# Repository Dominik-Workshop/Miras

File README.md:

# Miras

## Overview

Autonomous minisumo robot, based around an **STM32** microcontroller and **VL53L0X** TOF (time of flight) distance sensors, which provide necessary processing power and great detection range of opponents.

Its distinguishing feature is a set of **deployable wings**, designed to attract an opponent toward them, making them vulnerable to falling off the dohyo.

## Electronics

This project features two custom-designed PCBs that are connected via a flexible flat cable (FFC):

- [**Main board**](/pcb_main/): responsible for the robot's core functionalities. It integrates the microcontroller, sensors, motor drivers, and power management circuitry

- [**Top board**](/pcb_top/): accommodates an on/off switch, an SWD programming connector, configuration DIP switches, and a dedicated space for a standard [starter module](https://p1r.se/startmodule/)

The robot also features a 128x64px **OLED** screen for debugging.

## Mechanical

The chassis is a robust blend of 3D-printed components, steel, and aluminum, designed for durability and a low center of gravity. For superior traction on the dohyo, the robot is equipped with custom cast rubber tires. The unique deployable wings, made from lightweight paper, serve as the active deflection mechanism.

The robot is powered by two **N20** motors.

## Used Tools

- [Autodesk EAGLE](https://www.autodesk.com/products/eagle/) - Schematic and PCB design
- [Autodesk Inventor](https://www.autodesk.com/products/inventor/) - 3D modeling
- [STM32CubeIDE](https://www.st.com/en/development-tools/stm32cubeide.html) - STM32 firmware development (build/flash/debug)

## Authors

- [**Dominik Pluta**](https://github.com/Dominik-Workshop):
  - **Responsibility**: PCB design, programming
- [**Kamil Winnicki**](https://github.com/KamilWuu):
  - **Responsibility**: design and manufacturing of mechanical parts

## Special Thanks

Special thanks to [**Eryk Możdzeń**](https://github.com/Eryk-Mozdzen), who helped with programming.

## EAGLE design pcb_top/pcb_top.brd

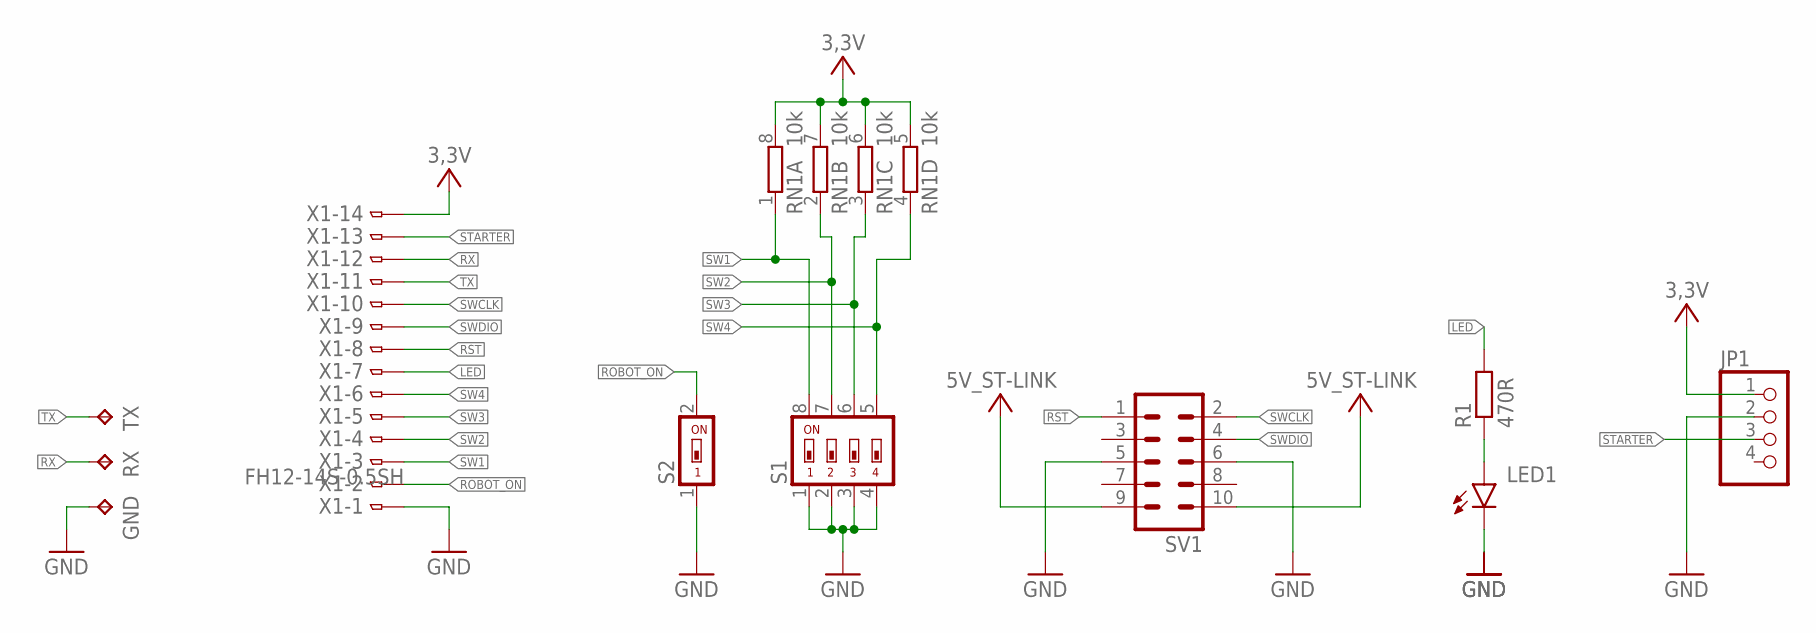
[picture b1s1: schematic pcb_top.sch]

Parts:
GND: TPTP20SQ; TP20SQ
JP1: PINHD-1X4; 1X04
LED1: LEDCHIP-LED0805; CHIP-LED0805
R1: 470R; R0603
RN1: 10k; CAT16
RX: TPTP20SQ; TP20SQ
S1: SWS004; SMS-004
S2: SWS001; SMS-001
SV1: ML10
TX: TPTP20SQ; TP20SQ
X1: FH12-14S-0.5SH

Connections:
3,3V: JP1.1, RN1.5 (2), RN1.6 (2), RN1.7 (2), RN1.8 (2), X1.14
5V_ST-LINK: SV1.9, SV1.10
GND: GND.TP, JP1.2, LED1.C, S1.1, S1.2, S1.3, S1.4, S2.1, SV1.5, SV1.6, X1.1
LED: R1.2, X1.7
unnamed: LED1.A, R1.1
ROBOT_ON: S2.2, X1.2
RST: SV1.1, X1.8
RX: RX.TP, X1.12
STARTER: JP1.3, X1.13
SW1: RN1.1, S1.8, X1.3
SW2: RN1.2 (1), S1.7, X1.4
SW3: RN1.3 (1), S1.6, X1.5
SW4: RN1.4 (1), S1.5, X1.6
SWCLK: SV1.2, X1.10
SWDIO: SV1.4, X1.9
TX: TX.TP, X1.11

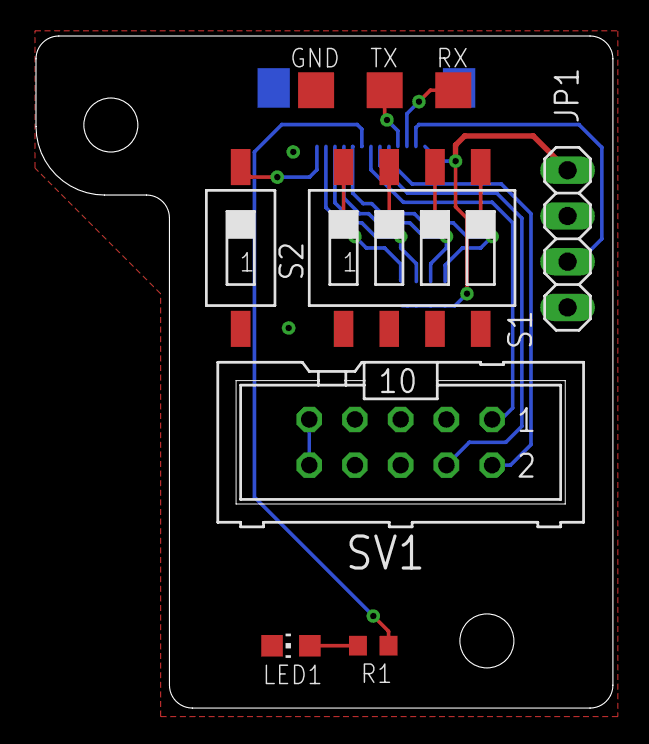
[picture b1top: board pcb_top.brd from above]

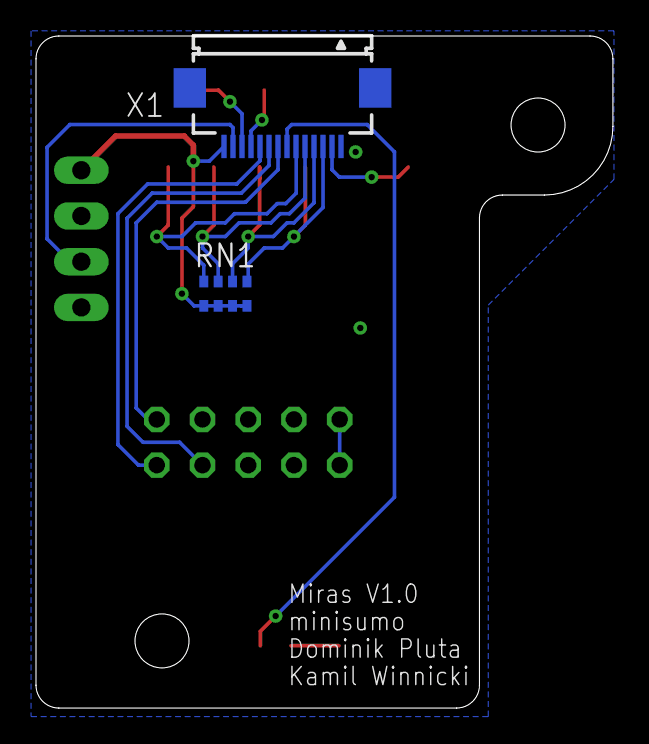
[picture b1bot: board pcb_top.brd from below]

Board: 2 copper layers, 32.0 x 37.3 mm, 11 parts (2 on the bottom side), 16 nets.

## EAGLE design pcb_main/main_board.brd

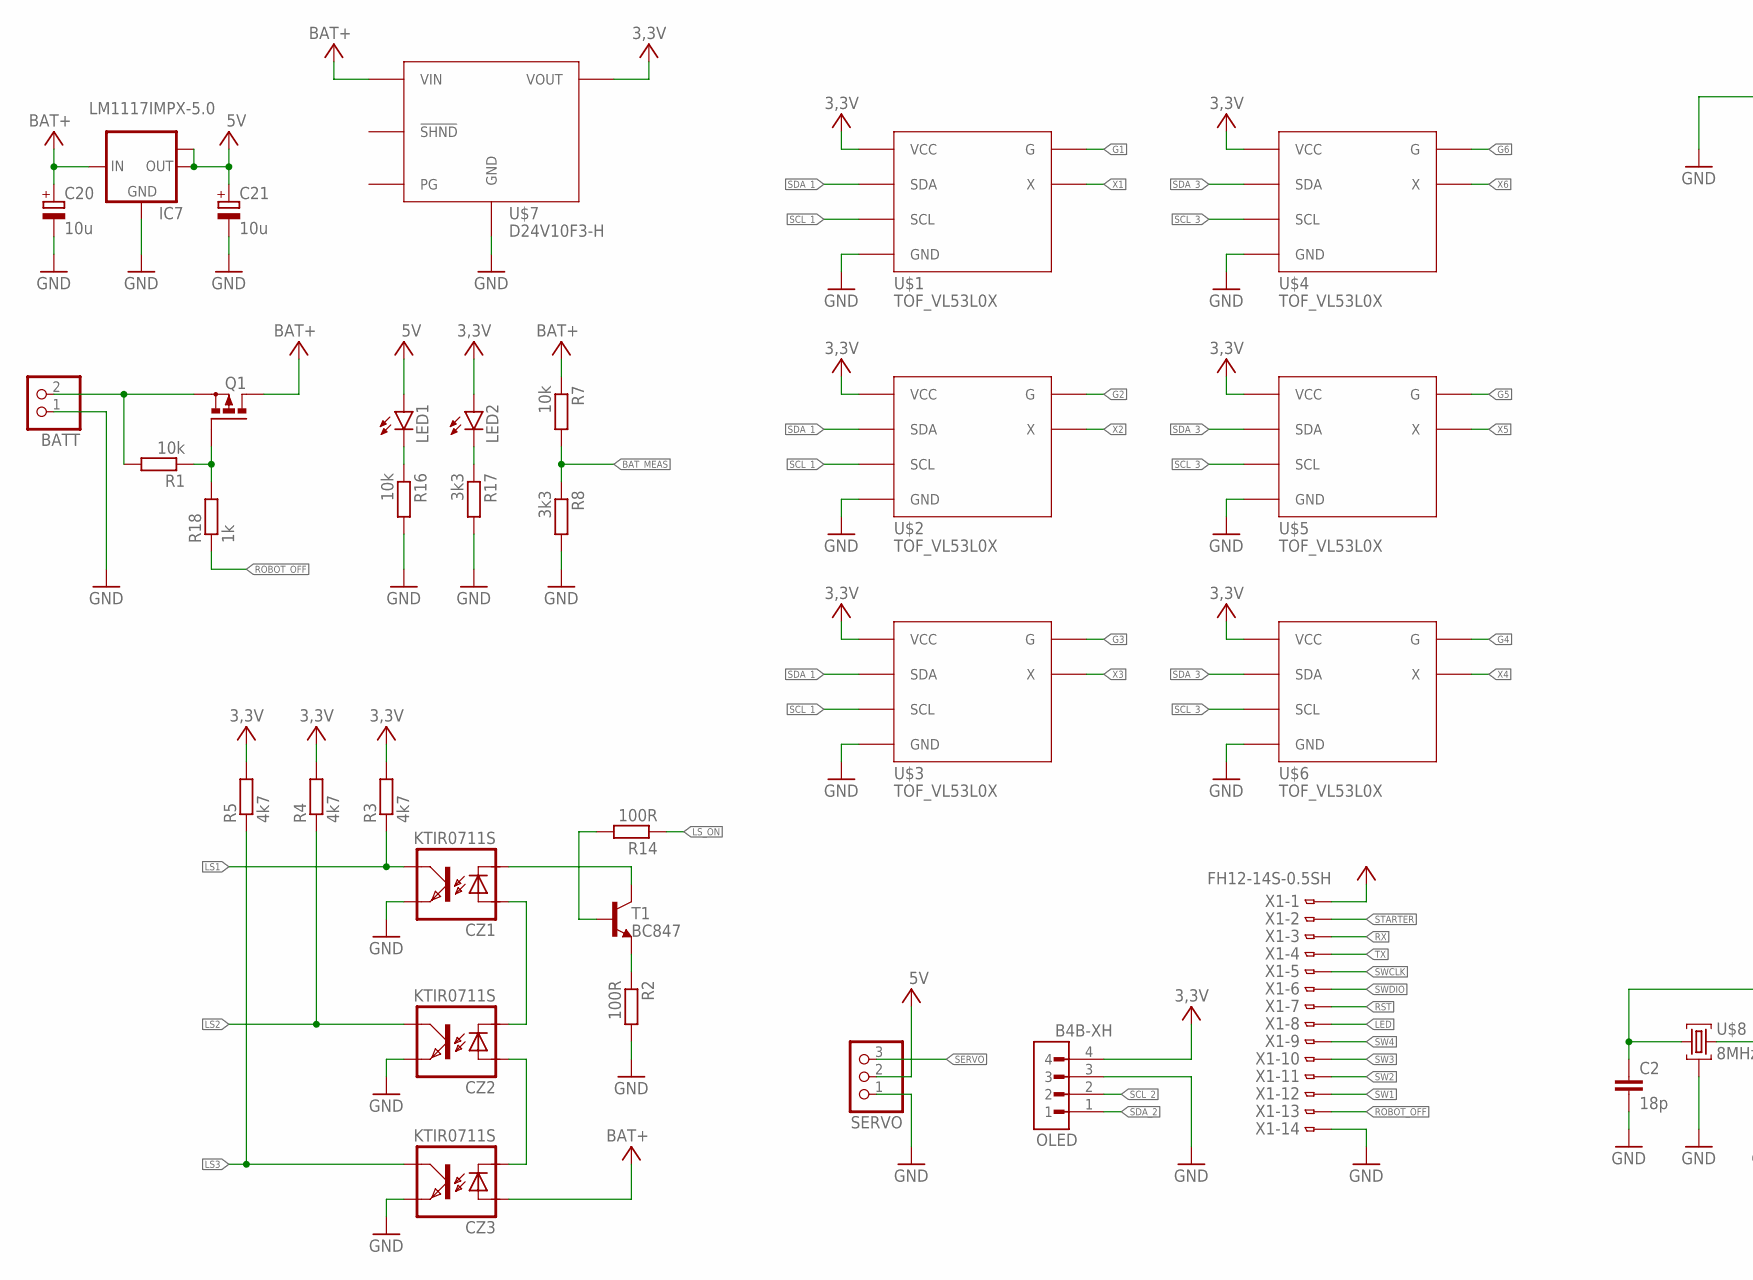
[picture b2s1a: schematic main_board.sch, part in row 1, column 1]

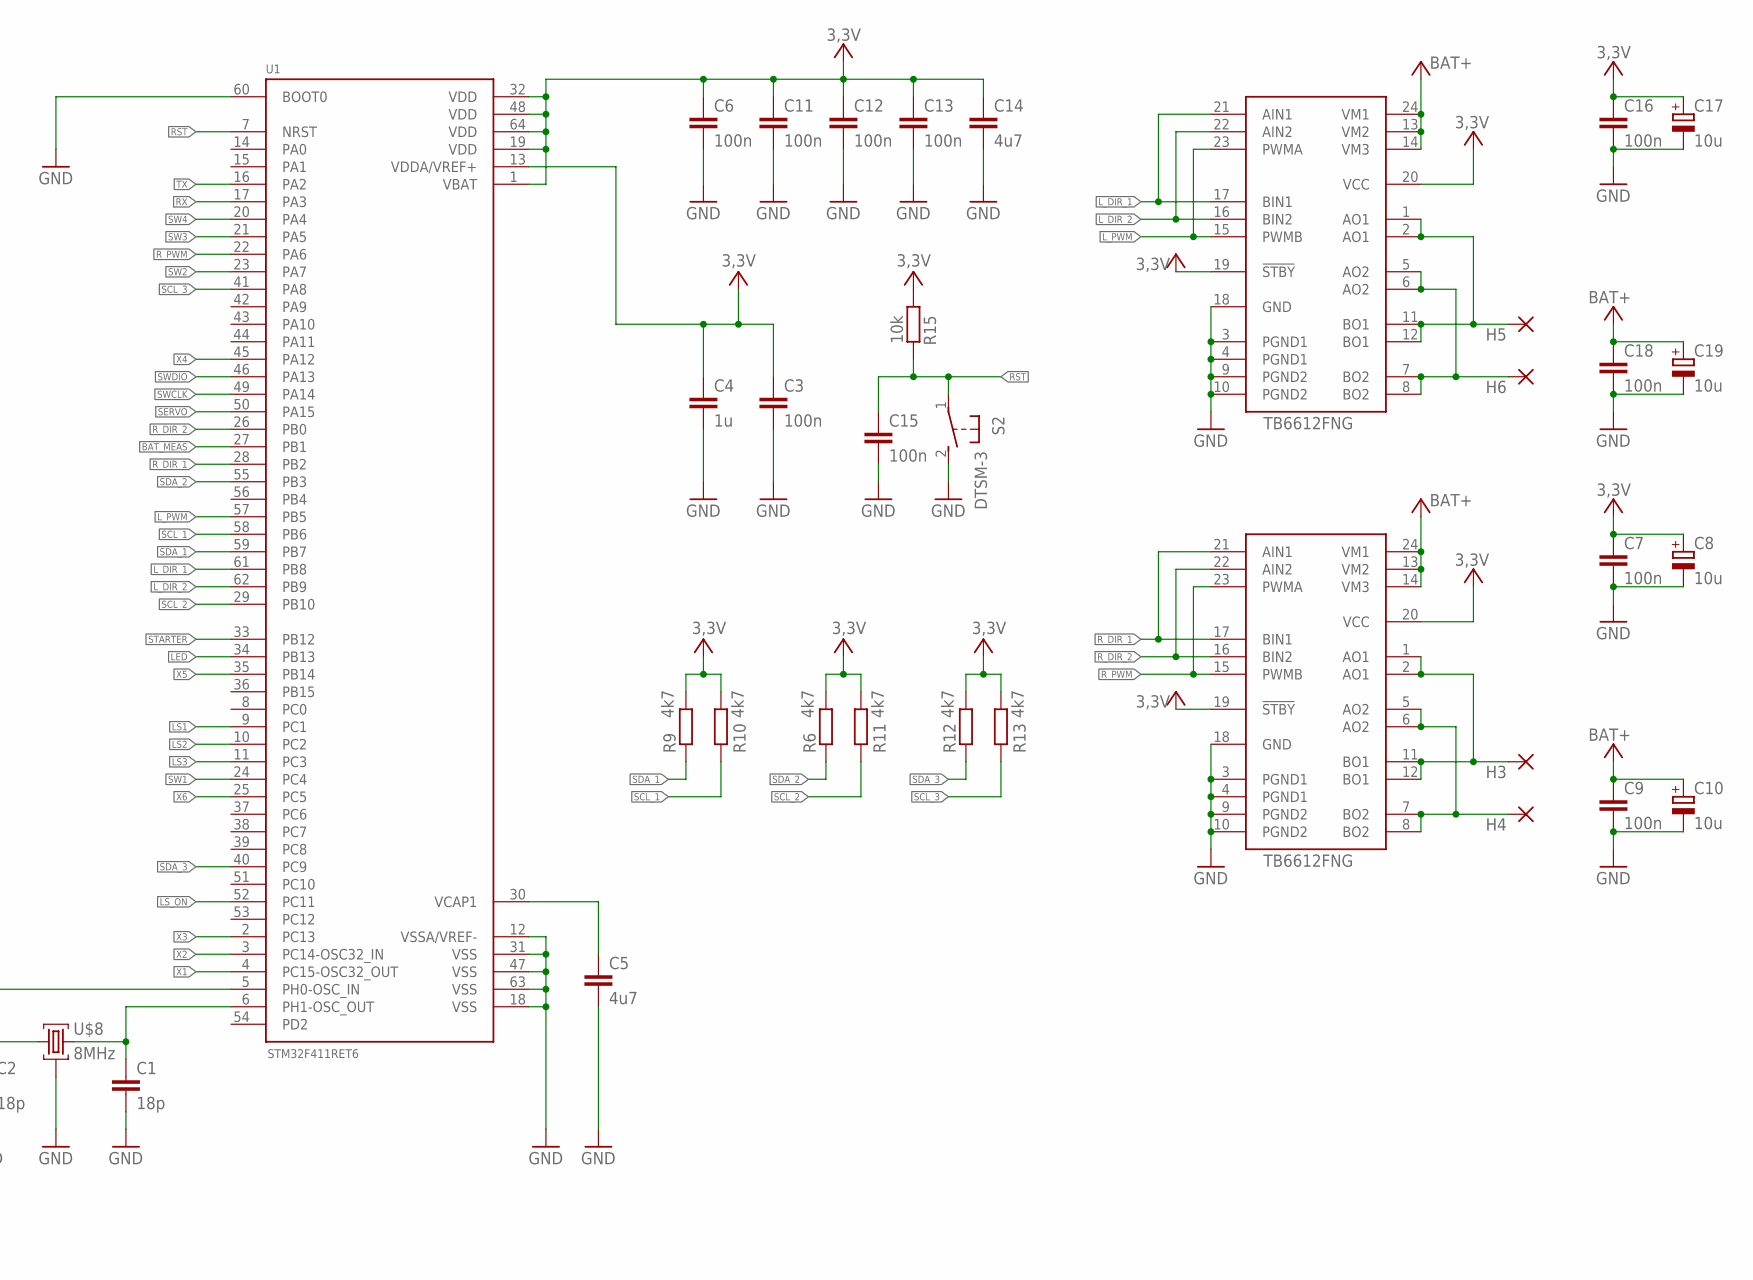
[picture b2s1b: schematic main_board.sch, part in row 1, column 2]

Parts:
BATT: PINHD-1X2; 1X02
C1, C2: 18p; C0603
C3, C6, C7, C9, C11, C12, C13, C15, C16, C18: 100n; C0603
C4: 1u; C0603
C5, C14: 4u7; C0603
C8, C10, C17, C19, C20, C21: 10u; B/3528-21W
CZ1, CZ2, CZ3: KTIR0711S; TOP
H3, H4, H5, H6: 1,6/0,8
IC7: LM1117IMPX-5.0; SOT223
LED1, LED2: LEDCHIPLED_0603; CHIPLED_0603
OLED: B4B-XH; JST_B4B-XH-A(LF)(SN)
Q1: P-MOSFET-SO8; SO-08
R1, R7, R15, R16: 10k; R0603
R2, R14: 100R; R0603
R3, R4, R5, R6, R9, R10, R11, R12, R13: 4k7; R0603
R8, R17: 3k3; R0603
R18: 1k; R0603
S2: DTSM-3
SERVO: PINHD-1X3; 1X03
T1: BC847; SOT23
TB6612, TB6612_: TB6612FNG; SSOP24
U1: STM32F411RET6; QFP50P1200X1200X160-64N
U$1, U$2, U$3, U$4, U$5, U$6: TOF_VL53L0X
U$7: D24V10F3-H
U$8: 8MHz; CRYSTAL_3,4X2,7
X1: FH12-14S-0.5SH

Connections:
3,3V: C3.1, C4.1, C6.1, C7.1, C8.+, C11.1, C12.1, C13.1, C14.1, C16.1, C17.+, LED2.A, OLED.4, R3.2, R4.2, R5.2, R6.2, R9.2, R10.2, R11.2, R12.2, R13.2, R15.1, TB6612.19 (!STBY), TB6612.20 (VCC), TB6612_.19 (!STBY), TB6612_.20 (VCC), U1.1 (VBAT), U1.13 (VDDA/VREF+), U1.19 (VDD), U1.32 (VDD), U1.48 (VDD), U1.64 (VDD), U$1.VCC, U$1.VCC_ (VCC), U$2.VCC, U$2.VCC_ (VCC), U$3.VCC, U$3.VCC_ (VCC), U$4.VCC, U$4.VCC_ (VCC), U$5.VCC, U$5.VCC_ (VCC), U$6.VCC, U$6.VCC_ (VCC), U$7.VOUT, X1.1
5V: C21.+, IC7.2 (OUT), IC7.TAB (OUT1), LED1.A, SERVO.2
BAT: BATT.2, Q1.1 (S), Q1.2 (S), Q1.3 (S), R1.2
BAT+: C9.1, C10.+, C18.1, C19.+, C20.+, CZ3.ANODA, IC7.3 (IN), Q1.5 (D), Q1.6 (D), Q1.7 (D), Q1.8 (D), R7.1, TB6612.13 (VM2), TB6612.14 (VM3), TB6612.24 (VM1), TB6612_.13 (VM2), TB6612_.14 (VM3), TB6612_.24 (VM1), U$7.VIN
BAT_MEAS: R7.2, R8.1, U1.27 (PB1)
BO1: H3.1, TB6612.1 (AO1), TB6612.2 (AO1), TB6612.11 (BO1), TB6612.12 (BO1)
BO2: H4.1, TB6612.5 (AO2), TB6612.6 (AO2), TB6612.7 (BO2), TB6612.8 (BO2)
BO3: H5.1, TB6612_.1 (AO1), TB6612_.2 (AO1), TB6612_.11 (BO1), TB6612_.12 (BO1)
BO4: H6.1, TB6612_.5 (AO2), TB6612_.6 (AO2), TB6612_.7 (BO2), TB6612_.8 (BO2)
G1: U$1.G
G2: U$2.G
G3: U$3.G
G4: U$6.G
G5: U$5.G
G6: U$4.G
GND: BATT.1, C1.2, C2.2, C3.2, C4.2, C5.2, C6.2, C7.2, C8.-, C9.2, C10.-, C11.2, C12.2, C13.2, C14.2, C15.2, C16.2, C17.-, C18.2, C19.-, C20.-, C21.-, CZ1.EMITER, CZ2.EMITER, CZ3.EMITER, IC7.1 (GND), OLED.3, R2.2, R8.2, R16.2, R17.2, S2.2, SERVO.1, TB6612.3 (PGND1), TB6612.4 (PGND1), TB6612.9 (PGND2), TB6612.10 (PGND2), TB6612.18 (GND), TB6612_.3 (PGND1), TB6612_.4 (PGND1), TB6612_.9 (PGND2), TB6612_.10 (PGND2), TB6612_.18 (GND), U1.12 (VSSA/VREF-), U1.18 (VSS), U1.31 (VSS), U1.47 (VSS), U1.60 (BOOT0), U1.63 (VSS), U$1.GND, U$1.GND_ (GND), U$2.GND, U$2.GND_ (GND), U$3.GND, U$3.GND_ (GND), U$4.GND, U$4.GND_ (GND), U$5.GND, U$5.GND_ (GND), U$6.GND, U$6.GND_ (GND), U$7.GND, U$8.GND (2), U$8.GND2 (2), X1.14
LED: U1.34 (PB13), X1.8
LS1: CZ1.KOLEKTOR, R3.1, U1.9 (PC1)
LS2: CZ2.KOLEKTOR, R4.1, U1.10 (PC2)
LS3: CZ3.KOLEKTOR, R5.1, U1.11 (PC3)
LS_ON: R14.1, U1.52 (PC11)
L_DIR_1: TB6612_.17 (BIN1), TB6612_.21 (AIN1), U1.61 (PB8)
L_DIR_2: TB6612_.16 (BIN2), TB6612_.22 (AIN2), U1.62 (PB9)
L_PWM: TB6612_.15 (PWMB), TB6612_.23 (PWMA), U1.57 (PB5)
unnamed: LED1.C, R16.1
unnamed: CZ1.KATODA, T1.3 (C)
unnamed: CZ1.ANODA, CZ2.KATODA
unnamed: CZ2.ANODA, CZ3.KATODA
unnamed: R14.2, T1.1 (B)
unnamed: R2.1, T1.2 (E)
unnamed: LED2.C, R17.1
unnamed: Q1.4 (G), R1.1, R18.2
ROBOT_OFF: R18.1, X1.13
RST: C15.1, R15.2, S2.1, U1.7 (NRST), X1.7
RX: U1.17 (PA3), X1.3
R_DIR_1: TB6612.17 (BIN1), TB6612.21 (AIN1), U1.28 (PB2)
R_DIR_2: TB6612.16 (BIN2), TB6612.22 (AIN2), U1.26 (PB0)
R_PWM: TB6612.15 (PWMB), TB6612.23 (PWMA), U1.22 (PA6)
SCL_1: R10.1, U1.58 (PB6), U$1.SCL, U$1.SCL_ (SCL), U$2.SCL, U$2.SCL_ (SCL), U$3.SCL, U$3.SCL_ (SCL)
SCL_2: OLED.2, R11.1, U1.29 (PB10)
SCL_3: R13.1, U1.41 (PA8), U$4.SCL, U$4.SCL_ (SCL), U$5.SCL, U$5.SCL_ (SCL), U$6.SCL, U$6.SCL_ (SCL)
SDA_1: R9.1, U1.59 (PB7), U$1.SDA, U$1.SDA_ (SDA), U$2.SDA, U$2.SDA_ (SDA), U$3.SDA, U$3.SDA_ (SDA)
SDA_2: OLED.1, R6.1, U1.55 (PB3)
SDA_3: R12.1, U1.40 (PC9), U$4.SDA, U$4.SDA_ (SDA), U$5.SDA, U$5.SDA_ (SDA), U$6.SDA, U$6.SDA_ (SDA)
SERVO: SERVO.3, U1.50 (PA15)
STARTER: U1.33 (PB12), X1.2
SW1: U1.24 (PC4), X1.12
SW2: U1.23 (PA7), X1.11
SW3: U1.21 (PA5), X1.10
SW4: U1.20 (PA4), X1.9
SWCLK: U1.49 (PA14), X1.5
SWDIO: U1.46 (PA13), X1.6
TX: U1.16 (PA2), X1.4
VCAP: C5.1, U1.30 (VCAP1)
X1: U1.4 (PC15-OSC32_OUT), U$1.X
X2: U1.3 (PC14-OSC32_IN), U$2.X
X3: U1.2 (PC13), U$3.X
X4: U1.45 (PA12), U$6.X
X5: U1.35 (PB14), U$5.X
X6: U1.25 (PC5), U$4.X
XTAL1: C2.1, U1.5 (PH0-OSC_IN), U$8.CRST1 (1)
XTAL2: C1.1, U1.6 (PH1-OSC_OUT), U$8.CRST2 (3)

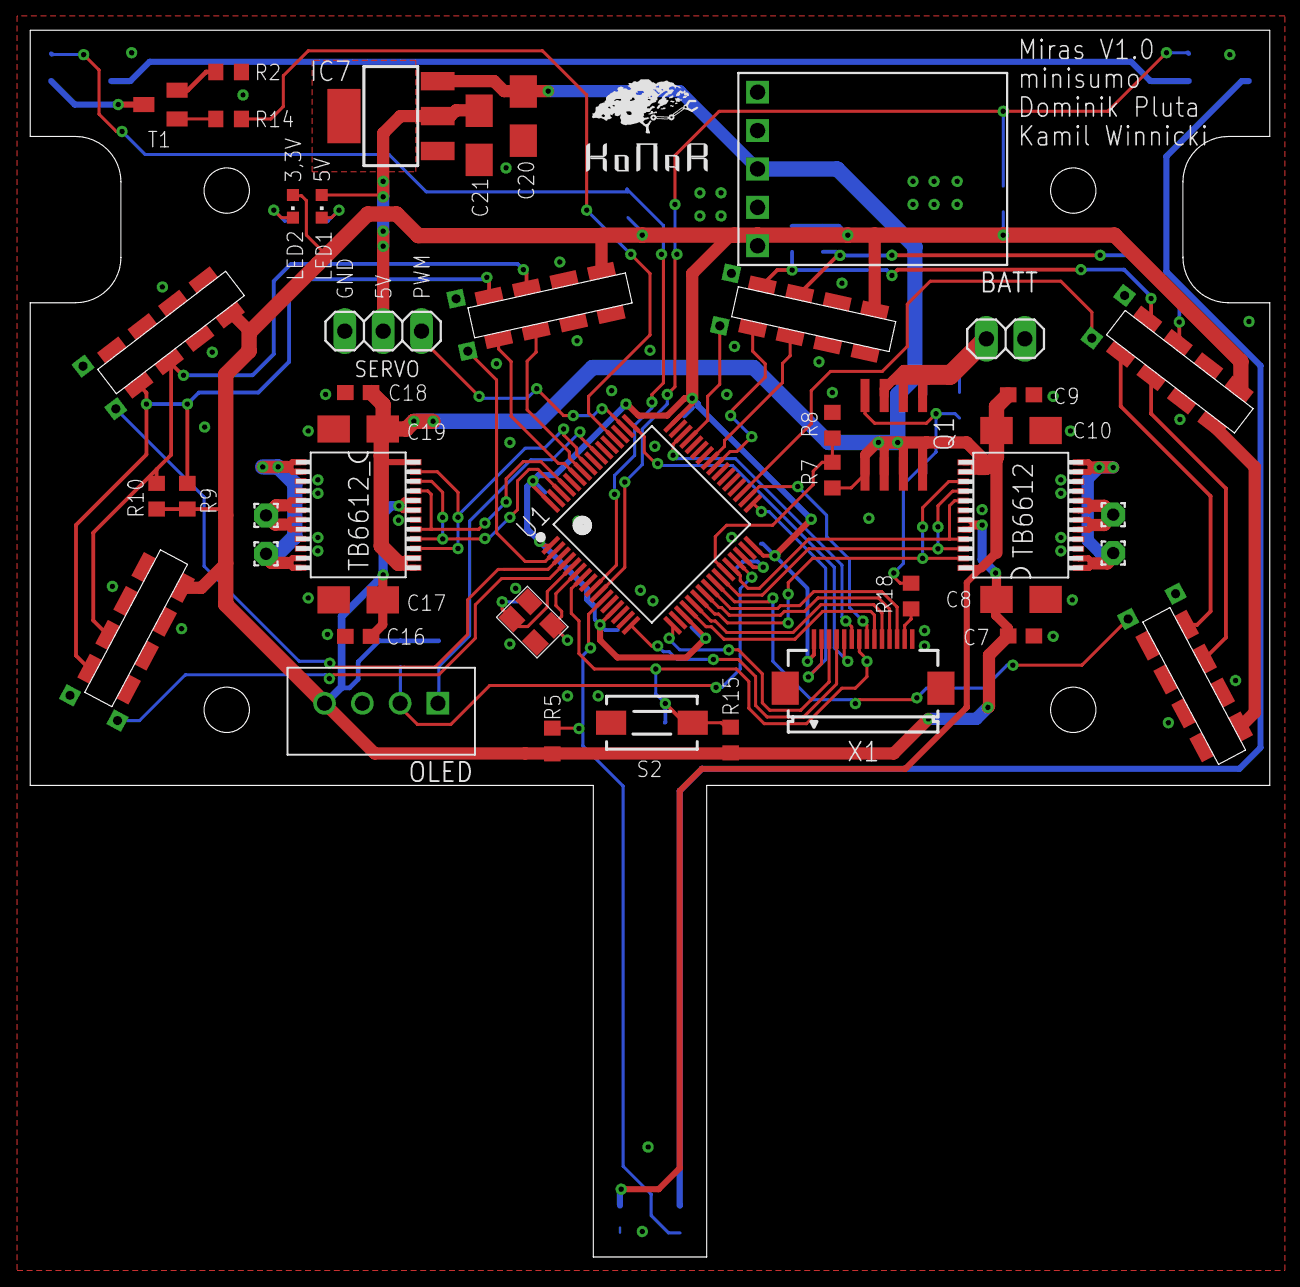
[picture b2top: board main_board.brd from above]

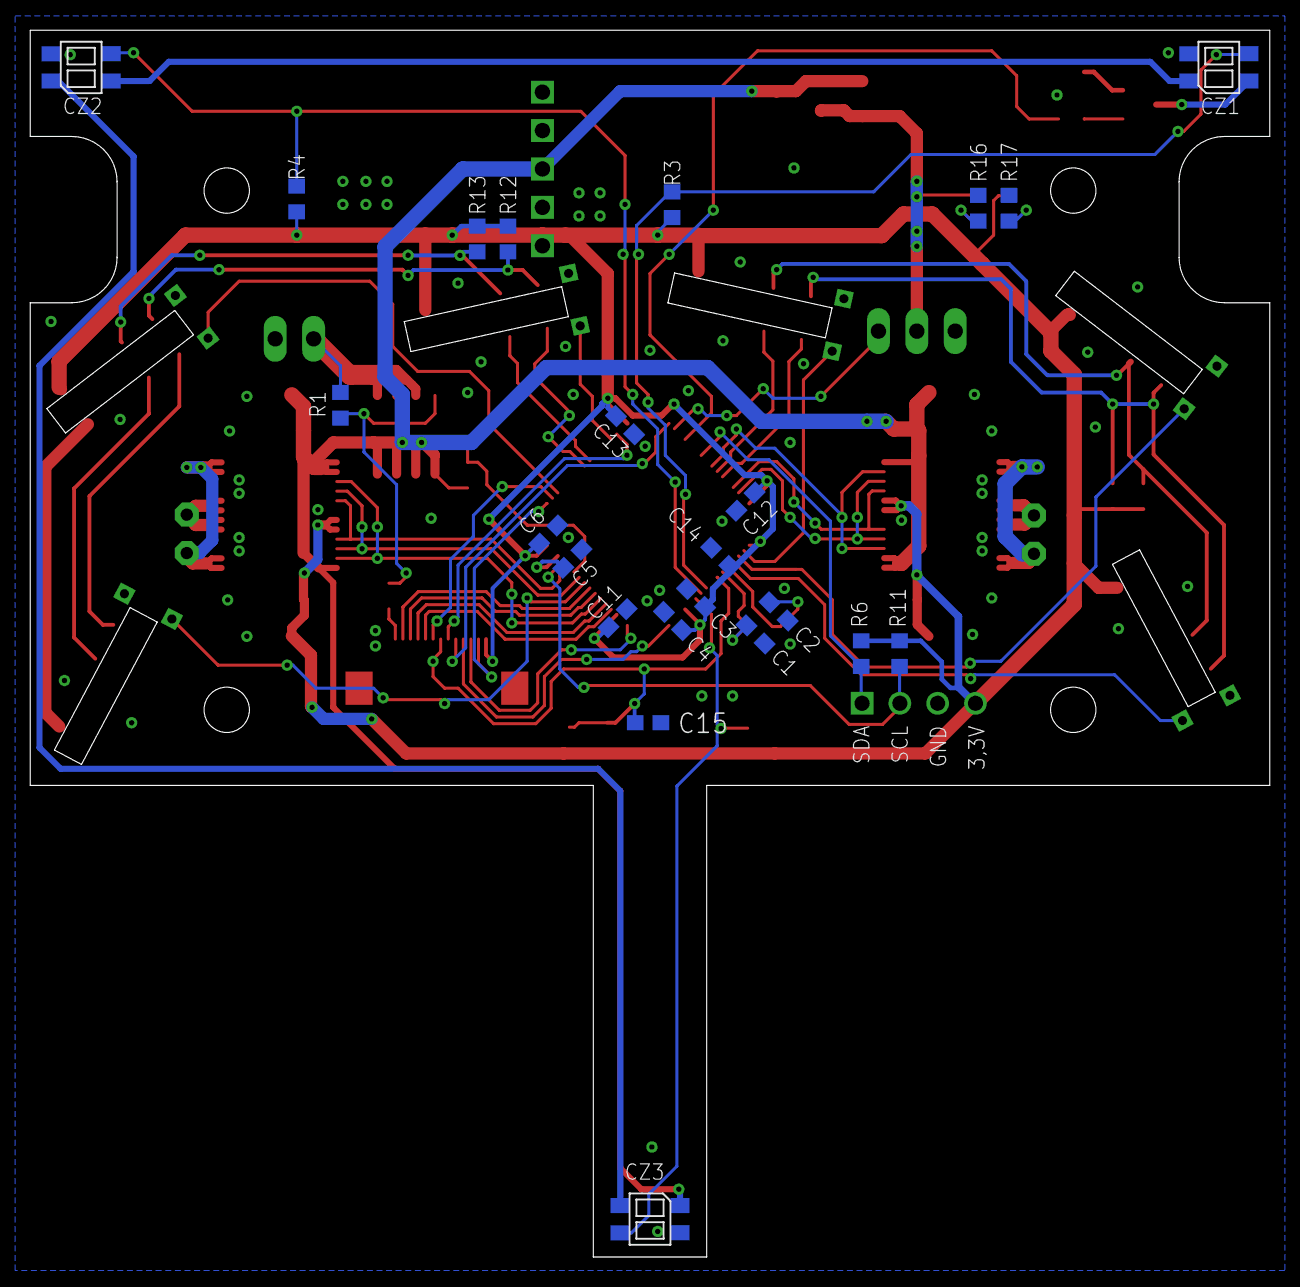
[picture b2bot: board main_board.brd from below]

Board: 2 copper layers, 82.0 x 81.2 mm, 67 parts (23 on the bottom side), 56 nets.

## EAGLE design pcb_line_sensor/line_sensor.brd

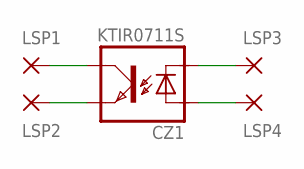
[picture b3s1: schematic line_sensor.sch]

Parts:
CZ1: KTIR0711S; TOP
LSP1, LSP2, LSP3, LSP4: 1,6/0,9

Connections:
unnamed: CZ1.KOLEKTOR, LSP1.1
unnamed: CZ1.EMITER, LSP2.1
unnamed: CZ1.KATODA, LSP3.1
unnamed: CZ1.ANODA, LSP4.1

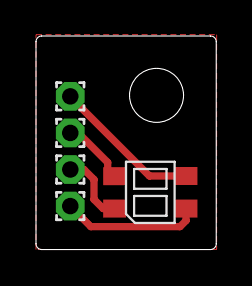
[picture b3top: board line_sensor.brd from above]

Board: 2 copper layers, 10.0 x 11.8 mm, 5 parts (0 on the bottom side), 4 nets.

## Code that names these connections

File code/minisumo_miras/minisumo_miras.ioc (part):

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Mcu.Name=STM32F411R(C-E)Tx
Mcu.Package=LQFP64
Mcu.UserName=STM32F411RETx
PA12.GPIOParameters=GPIO_Label
PA12.GPIO_Label=TOF_X4
PA12.Signal=GPIO_Output
PA13.Signal=SYS_JTMS-SWDIO
PA14.Signal=SYS_JTCK-SWCLK
PA15.GPIOParameters=GPIO_Label
PA15.GPIO_Label=servo
PA15.Signal=S_TIM2_CH1_ETR
PA2.Mode=Asynchronous
PA2.Signal=USART2_TX
PA3.Mode=Asynchronous
PA3.Signal=USART2_RX
PA4.GPIOParameters=GPIO_Label
PA4.GPIO_Label=SW4
PA4.Signal=GPIO_Input
PA5.GPIOParameters=GPIO_Label
PA5.GPIO_Label=SW3
PA5.Signal=GPIO_Input
PA6.GPIOParameters=GPIO_Label
PA6.GPIO_Label=motor_R_PWM
PA6.Signal=S_TIM3_CH1
PA7.GPIOParameters=GPIO_Label
PA7.GPIO_Label=SW2
PA7.Signal=GPIO_Input
PA8.Mode=I2C
PA8.Signal=I2C3_SCL
PB0.GPIOParameters=GPIO_Label
PB0.GPIO_Label=motor_R_DIR_2
PB0.Signal=GPIO_Output
PB1.GPIOParameters=GPIO_Label
PB1.GPIO_Label=adc_bat_meas
PB1.Signal=ADCx_IN9
PB10.Mode=I2C
PB10.Signal=I2C2_SCL
PB12.GPIOParameters=GPIO_Label
PB12.GPIO_Label=starter
PB12.Signal=GPIO_Input
PB13.GPIOParameters=GPIO_Label
PB13.GPIO_Label=user_LED
PB13.Signal=GPIO_Output
PB14.GPIOParameters=GPIO_Label
PB14.GPIO_Label=TOF_X5
PB14.Signal=GPIO_Output
PB2.GPIOParameters=GPIO_Label
PB2.GPIO_Label=motor_R_DIR_1
PB2.Signal=GPIO_Output
PB3.Mode=I2C
PB3.Signal=I2C2_SDA
PB5.GPIOParameters=GPIO_Label
PB5.GPIO_Label=motor_L_PWM
PB5.Signal=S_TIM3_CH2
PB6.Mode=I2C
PB6.Signal=I2C1_SCL
PB7.Mode=I2C
PB7.Signal=I2C1_SDA
PB8.GPIOParameters=GPIO_Label
PB8.GPIO_Label=motor_L_DIR_1
PB8.Signal=GPIO_Output
PB9.GPIOParameters=GPIO_Label
PB9.GPIO_Label=motor_L_DIR_2
PB9.Signal=GPIO_Output
PC1.GPIOParameters=GPIO_Label
PC1.GPIO_Label=adc_line_sensor1
PC1.Signal=ADCx_IN11
PC11.GPIOParameters=GPIO_Label
PC11.GPIO_Label=LS_ON
PC11.Signal=GPIO_Output
PC13-ANTI_TAMP.GPIOParameters=GPIO_Label
PC13-ANTI_TAMP.GPIO_Label=TOF_X3
PC13-ANTI_TAMP.Signal=GPIO_Output
PC14-OSC32_IN.GPIOParameters=GPIO_Label
PC14-OSC32_IN.GPIO_Label=TOF_X2
PC14-OSC32_IN.Signal=GPIO_Output
PC15-OSC32_OUT.GPIOParameters=GPIO_Label
PC15-OSC32_OUT.GPIO_Label=TOF_X1
PC15-OSC32_OUT.Signal=GPIO_Output
PC2.GPIOParameters=GPIO_Label
PC2.GPIO_Label=adc_line_sensor2
PC2.Signal=ADCx_IN12
PC3.GPIOParameters=GPIO_Label
PC3.GPIO_Label=adc_line_sensor3
PC3.Signal=ADCx_IN13
PC4.GPIOParameters=GPIO_Label
PC4.GPIO_Label=SW1
PC4.Signal=GPIO_Input
PC5.GPIOParameters=GPIO_Label
PC5.GPIO_Label=TOF_X6
PC5.Signal=GPIO_Output
PC9.Mode=I2C
PC9.Signal=I2C3_SDA
PH0\ -\ OSC_IN.GPIOParameters=GPIO_Label
PH0\ -\ OSC_IN.GPIO_Label=XTAL
PH0\ -\ OSC_IN.Mode=HSE-External-Oscillator
PH0\ -\ OSC_IN.Signal=RCC_OSC_IN
PH1\ -\ OSC_OUT.GPIOParameters=GPIO_Label
PH1\ -\ OSC_OUT.GPIO_Label=XTAL
PH1\ -\ OSC_OUT.Mode=HSE-External-Oscillator
PH1\ -\ OSC_OUT.Signal=RCC_OSC_OUT
RCC.HSE_VALUE=8000000
RCC.SYSCLKFreq_VALUE=100000000
RCC.SYSCLKSource=RCC_SYSCLKSOURCE_PLLCLK
board=custom

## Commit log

2022-11-15 added stm32f411
2022-11-29 renamed files, added H bridge
2022-11-29 eagle trash
2022-11-29 h bridge
2022-12-01 finished v1
2022-12-28 robot's name
2022-12-28 sensors on main pcb
2022-12-28 line sensor
2022-12-29 pcb shape
2023-01-16 power routed more or less
2023-02-24 branch fix xd
2023-03-11 almost there
2023-03-11 before 2 H-bridges
2023-03-12 2 h-bridges, 5V reg
2023-03-12 almost done
2023-03-13 main pcb done
2023-03-19 improved routing
2023-03-19 corrected on
2023-03-19 corrected on/off
2023-03-26 finished v1.0
2023-03-26 minor changes
2023-04-29 oled and battery meas. works
2023-04-29 refactor
2023-04-30 adc KTIR works
2023-05-01 TOF distance sensor works
2023-05-03 2nd TOF works
2023-05-03 refaktor
2023-05-05 servo works kinda
2023-05-05 battery defines
2023-05-06 servo and motors work
2023-05-07 fight and debug modes
2023-05-09 starter works, initial opponent search
2023-05-10 new algorythm, wait for start mode
2023-05-10 fixed clock, before more TOFs
2023-05-10 3 TOFs work
2023-05-11 cleanup, tof init func
2023-05-13 line sensing fixed
2023-05-13 cleanup
2023-05-14 tofs continuous mode
2023-05-14 działa XD
2023-05-17 France tournament 1st place code
2023-12-12 added IRL pictures
2024-03-15 adjust component values
2024-03-15 faster turn at start
2024-05-08 remove trash
2024-05-29 add special thanks
2025-03-12 proba zmiany silnikow
2025-03-16 zmiany silnika 1
2025-03-19 zmiany uchwytu gornego
2025-03-22 mech
2025-03-23 [#1] Cleanup PCB folder, init distance sensors PCB project
2025-03-23 [#1] Add gitignore for KiCad
2025-04-09 added pololu motors mount
2025-08-02 Improve the README
2025-08-02 Fix code folder structure, delete Debug folder
2025-11-17 Update Used Tools section in README
